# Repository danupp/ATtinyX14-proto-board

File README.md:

# ATtinyX14-proto-board
Prototype board for ATtiny214/414/814/1614 MCUs. Drawn with KiCad.

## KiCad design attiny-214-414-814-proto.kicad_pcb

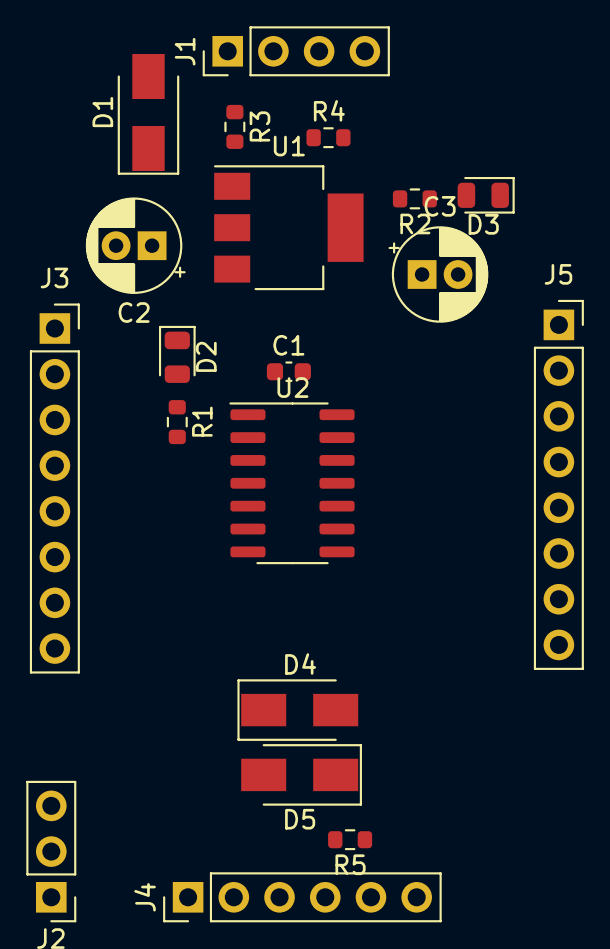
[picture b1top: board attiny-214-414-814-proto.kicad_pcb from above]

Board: 2 copper layers, 20 parts (0 on the bottom side), 22 nets, no tracks yet.

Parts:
C1: 100n; C_0603_1608Metric
C2, C3: 10µ/25V; CP_Radial_D5.0mm_P2.00mm
D1: standard diode; D_SMA
D2, D3: LED; LED_0805_2012Metric
D4, D5: D; D_SMA
J1: Conn_01x04_Male; PinHeader_1x04_P2.54mm_Vertical
J2: Conn_01x03_Male; PinHeader_1x03_P2.54mm_Vertical
J3, J5: Conn_01x08_Female; PinSocket_1x08_P2.54mm_Vertical
J4: Conn_01x06_Male; PinHeader_1x06_P2.54mm_Vertical
R1, R2, R4: 560; R_0603_1608Metric
R3: 1k; R_0603_1608Metric
R5: 4k7; R_0603_1608Metric
U1: LM317_SOT-223; SOT-223-3_TabPin2
U2: ATtiny214-SS; SOIC-14_3.9x8.7mm_P1.27mm

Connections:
GND: C1.2, C2.2, C3.2, D2.1, D3.1, J1.1, J1.4, J2.1, J3.1, J4.1, R3.1, U2.14
unnamed: C1.1, C3.1, D4.1, J1.3, J2.2, J3.2, R2.2, R4.2, U1.2, U2.1
unnamed: C2.1, D1.1, U1.3
unnamed: D1.2, J1.2
unnamed: D2.2, R1.1
unnamed: D3.2, R2.1
unnamed: D4.2, D5.1
unnamed: D5.2, J4.3
unnamed: J2.3, J4.5, J5.6, R5.1, U2.10
unnamed: J3.3, R1.2, U2.2
unnamed: J3.4, U2.3
unnamed: J3.5, U2.4
unnamed: J3.6, U2.5
unnamed: J3.7, U2.6
unnamed: J3.8, U2.7
unnamed: J4.4, R5.2
unnamed: J5.3, U2.13
unnamed: J5.4, U2.12
unnamed: J5.5, U2.11
unnamed: J5.7, U2.9
unnamed: J5.8, U2.8
unnamed: R3.2, R4.1, U1.1

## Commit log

2021-02-20 First release to git
